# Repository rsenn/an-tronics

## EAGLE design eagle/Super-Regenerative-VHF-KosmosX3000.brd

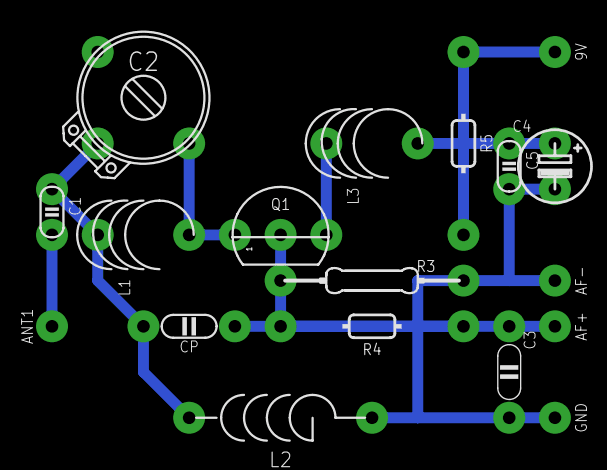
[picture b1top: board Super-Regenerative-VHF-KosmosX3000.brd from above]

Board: 2 copper layers, 18 parts (0 on the bottom side), 9 nets.

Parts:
9V: SPAD; SPAD@1
AF+: SPAD; SPAD@1
AF-: SPAD; SPAD@1
ANT1: ANT; SPAD
C1: 15p; C025-015X024
C2: 15p; TRIM-2222-808
C3: 6.8n; C050-020X036
C4: 100u; E2.5-4/V
C5: 100n; C025-015X024
CP: 4.7n; C050-020X036/V
GND: SPAD; SPAD@1
L1: L04/7; L-04-5/6V-C
L2: L-03/10
L3: 4 turns; L-04-5/6V-C
Q1: BF256B; TO92
R3: 3.3kΩ; 0204/10
R4: 10kΩ; 0202/10
R5: 150Ω; 0202/10

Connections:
GND: AF-.1, C3.2, C4.-, C5.2, GND.1, L2.2, R3.2
unnamed: CP.1, Q1.2, R3.1, R4.1
unnamed: AF+.1, C3.1, R4.2
unnamed: ANT1.1, C1.2
unnamed: C4.+, C5.1, L3.1, R5.1
unnamed: C2.3, L1.1, Q1.1
unnamed: C1.1, C2.2, CP.2, L1.2, L2.1
unnamed: L3.2, Q1.3
unnamed: 9V.1, R5.2

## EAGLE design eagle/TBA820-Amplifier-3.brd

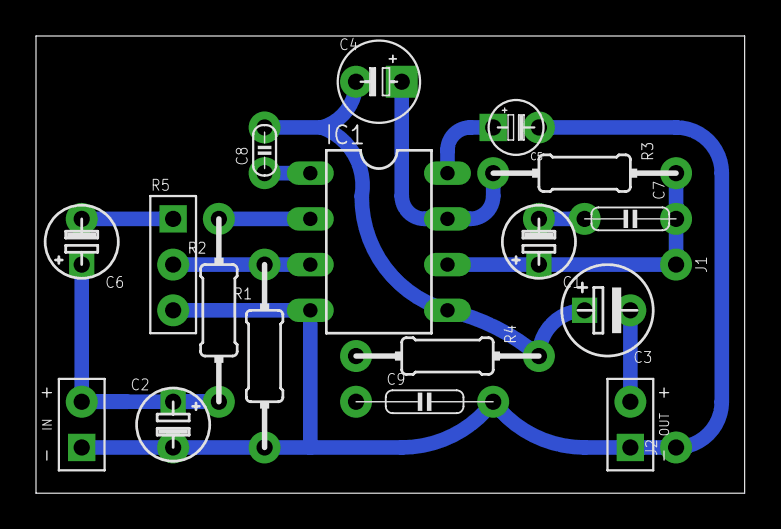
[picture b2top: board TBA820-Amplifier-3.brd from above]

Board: 2 copper layers, 39.4 x 25.4 mm, 19 parts (0 on the bottom side), 14 nets.

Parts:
C1, C2: 100μF; E2.5-4/V
C3: 220μF; E2,5-5
C4: 100μF; E2,5-4
C5: 47μF; E2,5-3
C6: 10μF; E2.5-4/V
C7: 100nF; C050-020X044/V
C8: 220pF; C025-015X024
C9: 220nF; C075-020X044
IC1: TBA820; DIL08
IN: SPAD+--+; SPAD-+
J1, J2: HPORT; SPAD
OUT: SPAD+-+-; SPAD+-
R1: 10kΩ; 0204/10-V
R2: 120Ω; 0204/10-V
R3: 56Ω; 0204/10-V
R4: 1Ω; 0204/10-V
R5: 22kΩ; CONN-3P

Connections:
BOOT: C4.+, IC1.7, R3.2
FREQ: C8.1, IC1.1
GAIN: IC1.2, R2.1
GND: C1.-, C7.2
INPUT: IC1.3, R1.1, R5.2
unnamed: C1.+, C7.1, IC1.6, J1.1, R3.1
unnamed: C2.-, C5.-, C9.2, IC1.4, IN.1, J2.1, OUT.1, R1.2, R5.3
unnamed: C9.1, R4.2
unnamed: C6.-, R5.1
unnamed: C6.+, IN.2
unnamed: C3.-, OUT.2
unnamed: C2.+, R2.2
OUT: C3.+, C4.-, C8.2, IC1.5, R4.1
RIPPLE: C5.+, IC1.8

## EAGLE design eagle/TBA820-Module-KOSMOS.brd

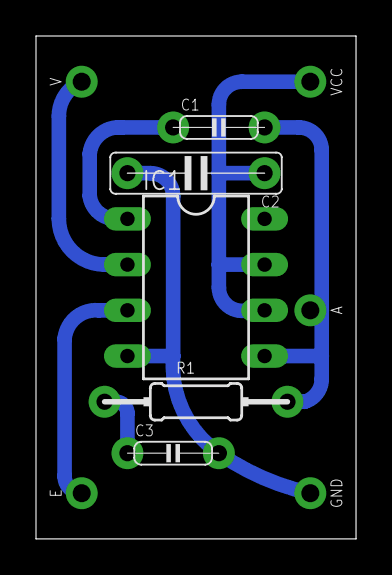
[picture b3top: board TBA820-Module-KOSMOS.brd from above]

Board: 2 copper layers, 17.8 x 27.9 mm, 10 parts (0 on the bottom side), 7 nets.

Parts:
A: SPAD
C1: 330pF; C050-020X044
C2: 100nF; C075-035X050
C3: 220nF; C050-020X044
E: SPAD
GND: SPAD
IC1: TBA820; DIL08
R1: 1Ω; 0204/10
V: SPAD
VCC: SPAD

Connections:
GND: C2.2, C3.2, GND.1, IC1.4
unnamed: C1.1, IC1.1
unnamed: A.1, C1.2, IC1.5, R1.2
unnamed: E.1, IC1.3
unnamed: C3.1, R1.1
unnamed: IC1.2, V.1
VCC: C2.1, IC1.6, IC1.7, VCC.1

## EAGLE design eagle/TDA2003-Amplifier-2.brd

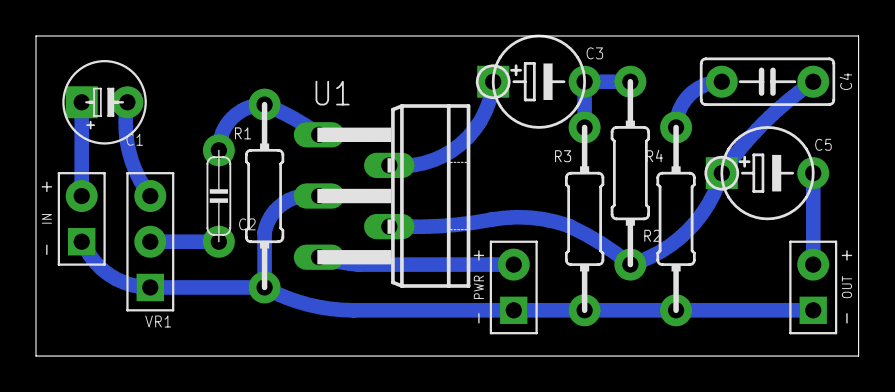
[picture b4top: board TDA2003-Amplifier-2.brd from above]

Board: 2 copper layers, 45.7 x 17.8 mm, 14 parts (0 on the bottom side), 11 nets.

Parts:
C1: 1µF/16V; E2,5-4
C2: 100nF; C050-020X044/V
C3: 220µF/16V; E5-5
C4: 10nF; C050-025X075/V
C5: 1000µF/16V; E5-5
IN: SPAD+--+; SPAD-+
OUT: SPAD+-+-; SPAD+-
PWR: VCC_GNDL; SPAD-+
R1: 100kΩ; 0204/10-V
R2: 220Ω; 0204/10-V
R3: 2.2Ω; 0204/10-V
R4: 1Ω; 0204/10-V
U1: TDA2003-B; TO220-B5
VR1: 10kΩ; CONN-3P

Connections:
AOUT: C4.1, C5.+, R2.1, U1.4
FB: C3.-, R2.2, R3.1
GND: IN.1, OUT.1, PWR.1, R1.2, R3.2, R4.2, U1.3, VR1.1
IN+: C2.2, R1.1, U1.1
IN-: C3.+, U1.2
unnamed: C4.2, R4.1
unnamed: C2.1, VR1.2
unnamed: C1.-, VR1.3
unnamed: C1.+, IN.2
OUT: C5.-, OUT.2
VCC: PWR.2, U1.5
